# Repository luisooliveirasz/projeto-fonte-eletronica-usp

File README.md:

# Projeto Fonte de Tensão Ajustável - 3V a 12V; 100mA;

> Projeto desenvolvido para a disciplina de Eletrônica para Computação — [USP-ICMC] · [2026.1]

---

## Integrantes

| Nome | NUSP |
|------|------|
| Luís Henrique Varela Medeiros Bezerra | 17908549 |
| Henrique Rossi Posso | 17868285 |
| Luís Fernando de Oliveira Souza | 17931682 |
| Malick Figueiredo Samoa | 16988652 |

---

## Descrição do Projeto

O projeto é uma fonte de tensão ajustável entre 3V e 12V, a partir de uma entrada AC 127V/60Hz. A montagem foi feita em uma protoboard, com simulação no Falstad para testes prévios e montagem no Eagle.

---

## Lista de Componentes

| Qtd | Componente | Valor / Especificação | Preço Unitário | Preço Total |
|-----|------------|----------------------|----------------|-------------|
| 1 | Transformador | 127V → 24V / 1A | R$ 0,00 | R$ 0,00 |
| 10 | Diodo retificador | 1N4007 | R$ 0,20 | R$ 2,00 |
| 1 | Capacitor eletrolítico | 1000 µF / 50V | R$ 6,60 | R$ 6,60 |
| 2 | Capacitor eletrolítico | 470 µF / 25V | R$ 2,00 | R$ 4,00 |
| 1 | Protoboard | BB-01 840 2 Barras | R$ 39,10 | R$ 39,10 |
| 3 | Diodo zener | 1N5243 / 13V½ ½W | R$ 0,40 | R$ 1,20 |
| 3 | Resistor | 4.7kΩ / 1W | R$ 0,40 | R$ 1,20 |
| 10 | Resistor | 1kΩ / ½W | R$ 0,07 | R$ 0,70 |
| 1 | Resistor | 3.3kΩ / 1/2W | R$ 0,00 | R$ 0,00 |
| 3 | Resistor | 100Ω / 5W | R$ 1,98 | R$ 5,94 |
| 3 | LED indicador | Vermelho 5mm | R$ 0,50 | R$ 1,50 |
| 3 | Transistor | 2N2222A NPN / 60V 0,8A | R$2,60 | R$7,80 |
| 2 | Pacote Jumper macho x macho | Kit 10pcs | R$7,00 | R$14.00 |
| 1 | Potenciômetro | 1W B10K / B-16,5XE-20XR-7MM | R$ 7,00 | R$ 7,00 |
| | | | **Total** | **R$ 89,84** |

---

OBS: os componentes cujo valores estão zerados foram emprestados ou cedidos por outros alunos ou pelo professor, e não utilizamos os capacitores de 470uF 25V;

## Justificativa dos Valores Escolhidos

- **Transformador:** _Escolhemos o transformador 2 da planilha do Simões._
- **Capacitor:** _Escolhemos o capacitor de 1000uF para garantir um ripple pequeno, e de 50V para aguentar com muita folga a tensão que pode passar por ele. O ripple mínimo era de 10%. O cálculo do ripple e da capacitância mínima será detalhado mais abaixo._
- **Resistores:** _Testamos os valores na simulação do falstad e decidimos pelos de 4.7k, e após teste real, trocamos um deles por de 3.3 para cumprir melhor as exigências do projeto._

---

## Cálculo do ripple e da capacitância mínima.

Após a retificação em ponte, a frequência da tensão pulsante passa a ser o dobro da frequência da rede. Assim, para uma rede de $60\text{ Hz}$,

$$
f_r = 2f = 120 \text{ Hz}
$$

A tensão no capacitor, lida diretamente no simulador Falstad, é:

$$
V_c = 26\text{ V}
$$

Admitindo corrente aproximadamente constante durante a descarga do capacitor, a partir da relação

$$
I=C\frac{dV}{dt},
$$

obtém-se a expressão aproximada para o ripple pico a pico:

$$
V_{r(pp)}=\frac{I}{f_rC}
$$

Na simulação, a corrente média medida no circuito foi de $32{,}074\text{ mA}$. Fixando um ripple máximo admissível de $10\%$ de $V_c$ e usando essa corrente:

$$
V_{r(pp)} = 0{,}10\times V_c = 0{,}10\times26 = 2{,}6\text{ V}
$$

a capacitância mínima necessária é

$$
C_{\min}=\frac{I}{f_rV_{r(pp)}}
=\frac{0{,}032074}{120\times2{,}6}
\approx1{,}03\times10^{-4}\text{ F}
=102{,}8\text{ }\mu\text{F}
$$

Como o valor comercial utilizado no projeto é $1000\text{ }\mu\text{F}$ (quase $10\times$ acima do mínimo), o ripple real obtido é bem menor:

$$
V_{r(pp)} = \frac{0{,}032074}{120\times1000\times10^{-6}} \approx 0{,}267\text{ V}
$$

o que corresponde a aproximadamente $1\%$ de $V_c$.

Portanto, para as condições simuladas, obtém-se um ripple aproximado de

$$
\boxed{V_{r(pp)}\approx0{,}27\text{ V}}
$$

---

## Simulação no Falstad

Acesse o circuito simulado clicando no link abaixo:

🔗 **[Abrir simulação no Falstad](https://is.gd/5gRgDR)**

---

## Projeto no EAGLE

Os arquivos do esquemático e da PCB estão disponíveis na pasta [`/eagle`](./eagle/):

```
eagle/
├── fonte.sch        # Esquemático
├── fonte.brd        # Layout da PCB
└── fonte.epf        # Arquivo do projeto no Eagle
```

### Esquemático

### Layout da PCB

---

## 📸 Fotos do Circuito Montado

### Protoboard

---

## Vídeo do Projeto

Assista ao vídeo de apresentação do projeto, onde explicamos o funcionamento e os componentes do circuito:

E assista também o vídeo de demonstração de funcionamento do circuito, com o ajuste de 3V a 12V:

---

## 📚 Referências

- [Datasheet — LM317](https://www.ti.com/product/LM317)
- [Datasheet — 1N4007](https://www.vishay.com/docs/88503/1n4001.pdf)
- [Simulador Falstad](https://www.falstad.com/circuit/)
- [EAGLE — Autodesk](https://www.autodesk.com/products/eagle/overview)

- OBS: O Eagle foi descontinuado pela autodesk. Conseguimos fazer o projeto nele um pouco antes disso, mas é melhor utilizar outros aplicativos indicados pelo professor agora.

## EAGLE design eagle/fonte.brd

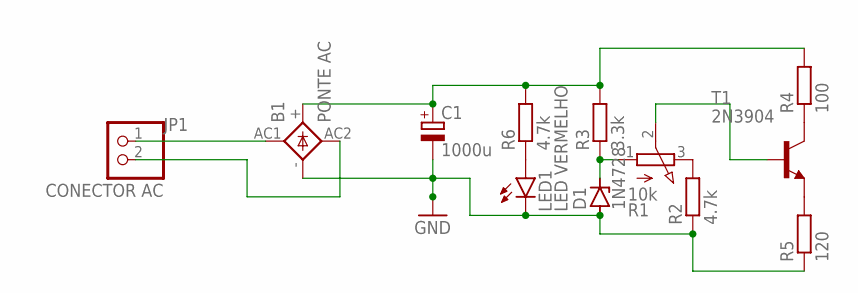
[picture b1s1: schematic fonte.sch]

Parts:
B1: PONTE AC; 1KAB
C1: 1000u; E5-10,5
D1: 1N4728; DO41Z10
JP1: CONECTOR AC; 1X02
LED1: LED VERMELHO; LED5MM
R1: 10k; 3RP/1610N
R2, R6: 4.7k; 0207/10
R3: 3.3k; 0207/10
R4: 100; 0207/10
R5: 120; 0207/10
T1: 2N3904; TO92

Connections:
GND: B1.-, C1.-, D1.A, LED1.K (C), R2.1, R5.1
unnamed: B1.AC1, JP1.1
unnamed: B1.AC2, JP1.2
unnamed: B1.+, C1.+, R3.2, R4.2, R6.2
unnamed: LED1.A, R6.1
unnamed: D1.C, R1.1 (A), R3.1
unnamed: R1.3 (E), R2.2
unnamed: R1.2 (S), T1.2 (B)
unnamed: R5.2, T1.3 (E)
unnamed: R4.1, T1.1 (C)

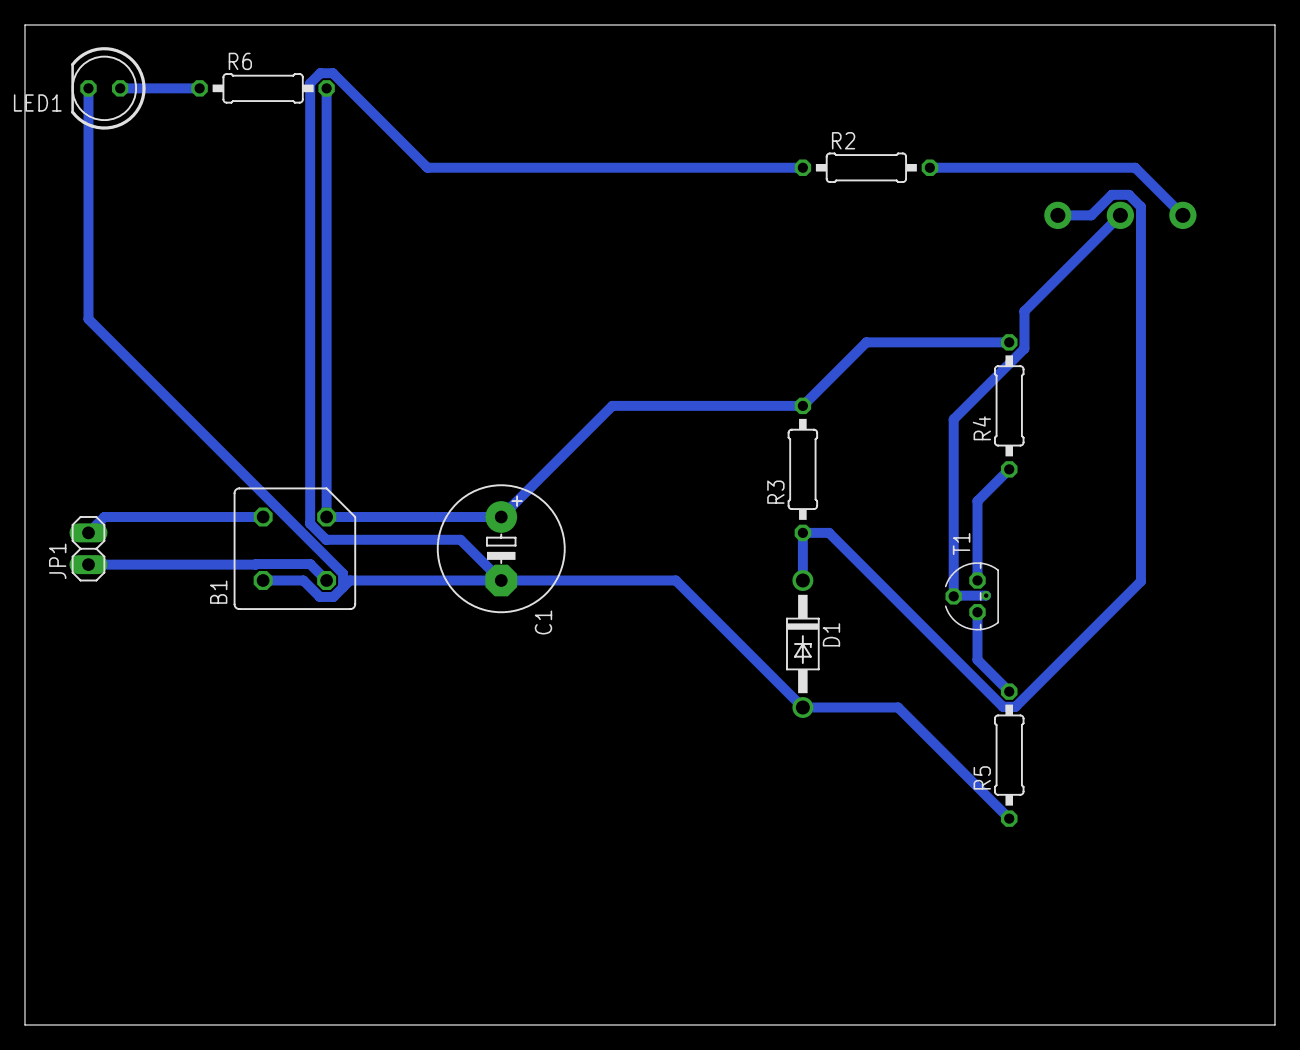
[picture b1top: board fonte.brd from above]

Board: 2 copper layers, 100.0 x 80.0 mm, 12 parts (1 on the bottom side), 10 nets.

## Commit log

2026-06-03 Update README.md
    Add equation image to README
2026-06-24 Update do README
2026-06-24 Revise README with project and component details
    Updated project details, team members, component list, and justification for component choices.
2026-06-29 temporario para adição de imagens
2026-06-29 Adição dos arquivos de imagens
2026-06-29 Update circuit diagram image in README
2026-06-29 Revise README with updated images and links
    Updated images and links in the README file, removed unnecessary sections, and improved clarity.
2026-06-29 Change image extensions in README.md
    Updated image file extensions from .jpg to .jpEg for consistency.
2026-06-29 Fix image extensions and update YouTube link
    Updated image file extensions and YouTube link format in README.
2026-06-29 Update project video description in README
2026-06-29 arquivo temporario
2026-06-29 Update README to include EPF file in Eagle project
